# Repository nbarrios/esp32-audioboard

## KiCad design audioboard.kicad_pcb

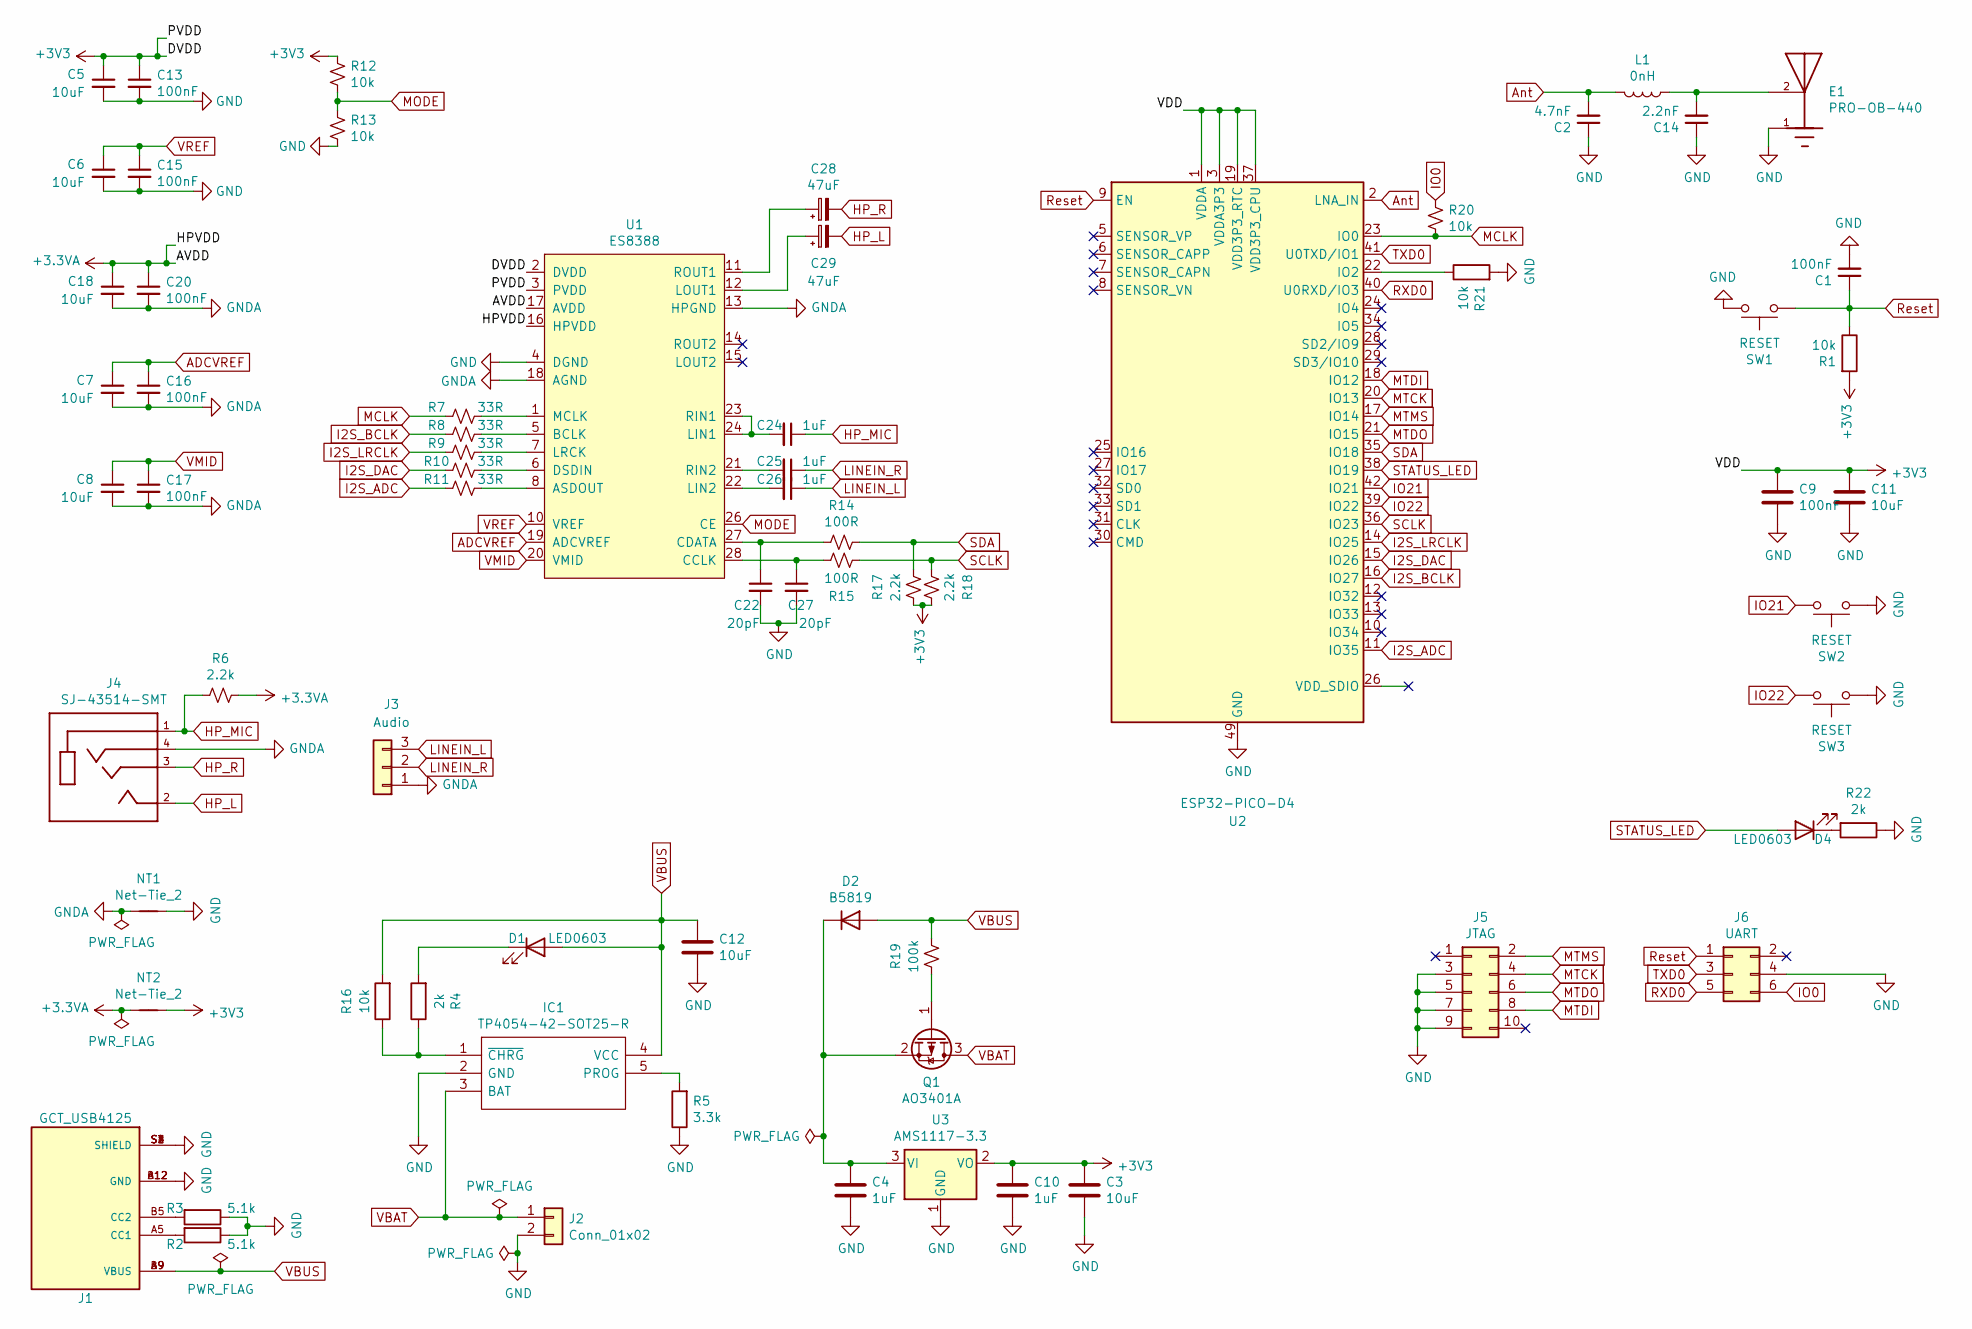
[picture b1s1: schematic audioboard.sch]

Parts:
C1, C9, C13, C15, C16, C17, C20: 100nF; C_0402_1005Metric; LCSC C1525
C2: 4.7nF; C_0402_1005Metric; LCSC C1538
C3, C5, C6, C7, C8, C11, C12, C18: 10uF; C_0402_1005Metric; LCSC C15525
C4, C10, C24, C25, C26: 1uF; C_0402_1005Metric; LCSC C52923
C14: 2.2nF; C_0402_1005Metric; LCSC C1531
C22, C27: 20pF; C_0402_1005Metric; LCSC C1554
C28, C29: 47uF; C_1206_3216Metric; LCSC C96123
D1, D4: LED0603; LED_0603_1608Metric; LCSC C2286
D2: B5819; D_SOD-123; LCSC C8598
E1: PRO-OB-440; ANT_PRO-OB-440; PARTREV 3.2
IC1: TP4054-42-SOT25-R; SOT95P280X100-5N; Manufacturer_Part_Number TP4054-42-SOT25-R; LCSC C32574
J1: GCT_USB4125; GCT_USB4125-GF-A_REVA
J2: Conn_01x02; Molex_PicoBlade_53261-0271_1x02-1MP_P1.25mm_Horizontal
J3: Audio; PinHeader_1x03_P2.54mm_Vertical
J4: SJ-43514-SMT; CUI_SJ-43514-SMT
J5: JTAG; PinHeader_2x05_P1.27mm_Vertical_SMD
J6: UART; PinHeader_2x03_P1.27mm_Vertical_SMD
L1: 0nH; L_0402_1005Metric; LCSC C17168
NT1, NT2: Net-Tie_2; NetTie-2_SMD_Pad0.5mm
Q1: AO3401A; SOT-23; LCSC C15127
R1, R12, R13, R16, R20, R21: 10k; R_0402_1005Metric; LCSC C25744
R2, R3: 5.1k; R_0603_1608Metric; LCSC C23186
R4, R22: 2k; R_0402_1005Metric; LCSC C4109
R5: 3.3k; R_0402_1005Metric; LCSC C25890
R6, R17, R18: 2.2k; R_0402_1005Metric; LCSC C25879
R7, R8, R9, R10, R11: 33R; R_0402_1005Metric; LCSC C25879
R14, R15: 100R; R_0402_1005Metric; LCSC C25076
R19: 100k; R_0402_1005Metric; LCSC C25741
SW1, SW2, SW3: RESET; TS1088R02026
U1: ES8388; QFN-28-1EP_4x4mm_P0.45mm_EP2.4x2.4mm; LCSC C365736
U2: ESP32-PICO-D4; QFN-48-1EP_7x7mm_P0.5mm_EP5.3x5.3mm; LCSC C193707
U3: AMS1117-3.3; SOT-223; LCSC C6186

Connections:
+3.3VA: C18.1, C20.1, NT2.1, R6.2, U1.16 (HPVDD), U1.17 (AVDD)
+3V3: C3.1, C5.1, C9.1, C10.1, C11.1, C13.1, NT2.2, R1.2, R12.1, R17.1, R18.2, U1.2 (DVDD), U1.3 (PVDD), U2.1 (VDDA), U2.3 (VDDA3P3), U2.4 (VDDA3P3), U2.19 (VDD3P3_RTC), U2.37 (VDD3P3_CPU), U2.43 (VDDA), U2.46 (VDDA), U3.2 (VO)
ADCVREF: C7.1, C16.1, U1.19 (ADCVREF)
Ant: C2.2, L1.2, U2.2 (LNA_IN)
GND: C1.2, C2.1, C3.2, C4.2, C5.2, C6.2, C9.2, C10.2, C11.2, C12.2, C13.2, C14.1, C15.2, C22.2, C27.2, E1.1, IC1.2 (GND), J1.A12 (GND), J1.B12 (GND), J1.S1 (SHIELD), J1.S2 (SHIELD), J1.S3 (SHIELD), J1.S4 (SHIELD), J2.2, J5.3, J5.5, J5.7, J5.9, J6.4, NT1.2, R2.1, R3.1, R5.1, R13.2, R21.2, R22.1, SW1.2, SW2.1, SW3.1, U1.4 (DGND), U2.49 (GND), U3.1 (GND)
GNDA: C7.2, C8.2, C16.2, C17.2, C18.2, C20.2, J3.1, J4.4, NT1.1, U1.13 (HPGND), U1.18 (AGND)
HP_L: C29.2, J4.2
HP_MIC: C24.1, J4.1, R6.1
HP_R: C28.2, J4.3
I2S_ADC: R11.2, U2.11 (IO35)
I2S_BCLK: R8.2, U2.16 (IO27)
I2S_DAC: R10.2, U2.15 (IO26)
I2S_LRCLK: R9.2, U2.14 (IO25)
IO0: J6.6, R20.1
IO21: SW2.2, U2.42 (IO21)
IO22: SW3.2, U2.39 (IO22)
LINEIN_L: C26.1, J3.3
LINEIN_R: C25.1, J3.2
MCLK: R7.2, R20.2, U2.23 (IO0)
MODE: R12.2, R13.1, U1.26 (CE)
MTCK: J5.4, U2.20 (IO13)
MTDI: J5.8, U2.18 (IO12)
MTDO: J5.6, U2.21 (IO15)
MTMS: J5.2, U2.17 (IO14)
unnamed: C4.1, D2.1 (K), Q1.2 (S), U3.3 (VI)
unnamed: C14.2, E1.2, L1.1
unnamed: C22.1, R14.2, U1.27 (CDATA)
unnamed: C24.2, U1.23 (RIN1), U1.24 (LIN1)
unnamed: C25.2, U1.21 (RIN2)
unnamed: C26.2, U1.22 (LIN2)
unnamed: C27.1, R15.2, U1.28 (CCLK)
unnamed: C28.1, U1.11 (ROUT1)
unnamed: C29.1, U1.12 (LOUT1)
unnamed: D1.1 (K), R4.2
unnamed: D4.1 (K), R22.2
unnamed: IC1.1 (~CHRG), R4.1, R16.1
unnamed: IC1.5 (PROG), R5.2
unnamed: J1.A5 (CC1), R2.2
unnamed: J1.B5 (CC2), R3.2
unnamed: Q1.1 (G), R19.1
unnamed: R7.1, U1.1 (MCLK)
unnamed: R8.1, U1.5 (BCLK)
unnamed: R9.1, U1.7 (LRCK)
unnamed: R10.1, U1.6 (DSDIN)
unnamed: R11.1, U1.8 (ASDOUT)
unnamed: R21.1, U2.22 (IO2)
RXD0: J6.5, U2.40 (U0RXD/IO3)
Reset: C1.1, J6.1, R1.1, SW1.1, U2.9 (EN)
SCLK: R15.1, R18.1, U2.36 (IO23)
SDA: R14.1, R17.2, U2.35 (IO18)
STATUS_LED: D4.2 (A), U2.38 (IO19)
TXD0: J6.3, U2.41 (U0TXD/IO1)
VBAT: IC1.3 (BAT), J2.1, Q1.3 (D)
VBUS: C12.1, D1.2 (A), D2.2 (A), IC1.4 (VCC), J1.A9 (VBUS), J1.B9 (VBUS), R16.2, R19.2
VMID: C8.1, C17.1, U1.20 (VMID)
VREF: C6.1, C15.1, U1.10 (VREF)

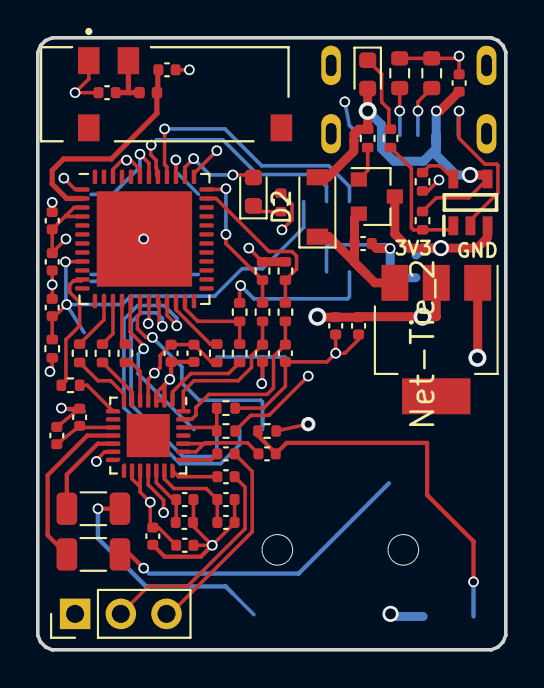
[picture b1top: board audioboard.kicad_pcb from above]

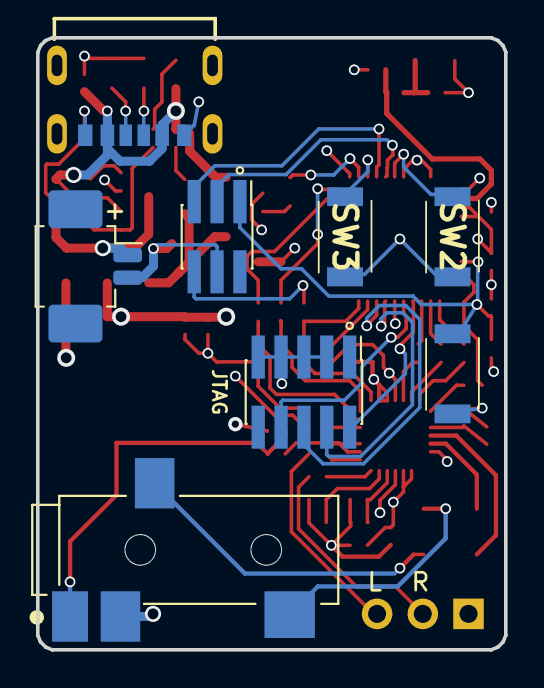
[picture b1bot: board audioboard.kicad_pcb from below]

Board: 4 copper layers, 26.0 x 34.0 mm, 69 parts (9 on the bottom side), 56 nets.

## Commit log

2021-02-27 Initial commit.
2021-03-10 Add v2
2022-06-20 Create LICENSE
